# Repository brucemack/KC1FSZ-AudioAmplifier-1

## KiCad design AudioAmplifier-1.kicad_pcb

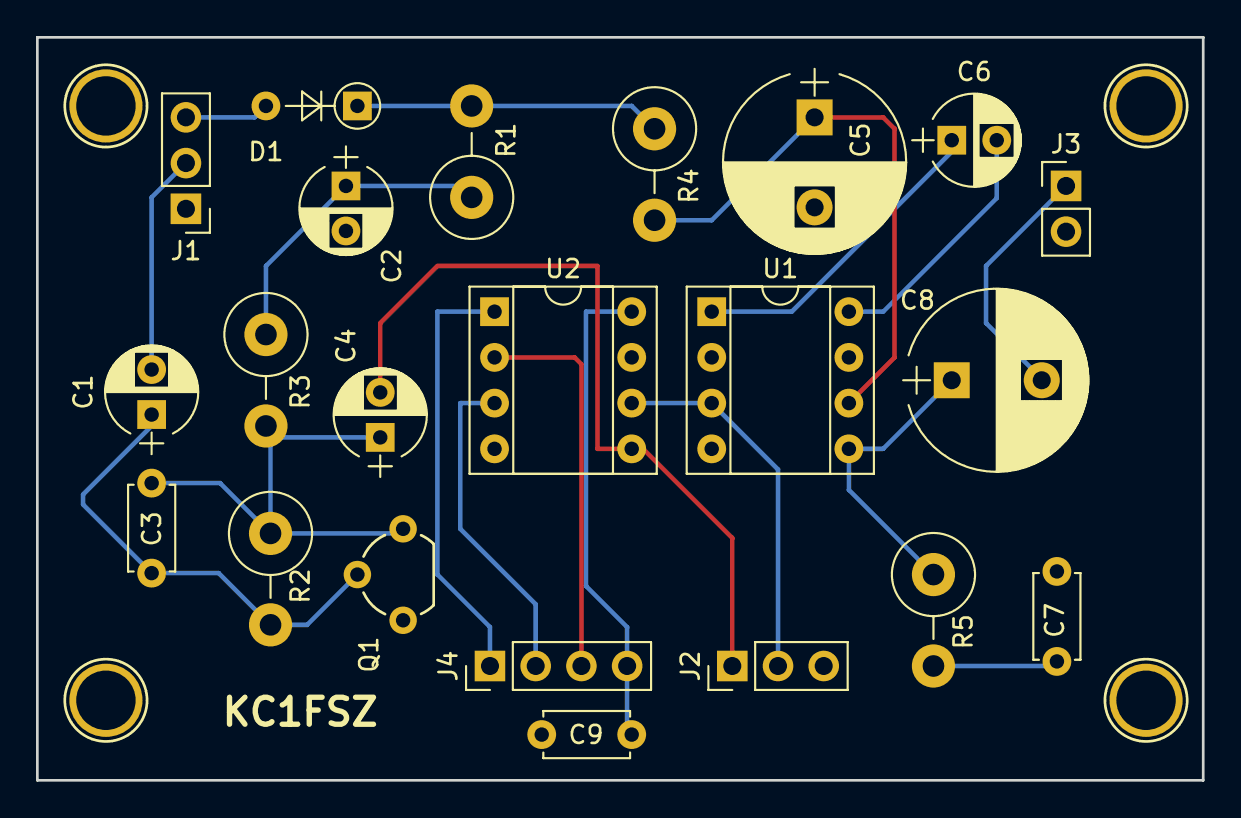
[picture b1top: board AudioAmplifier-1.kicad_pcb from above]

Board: 2 copper layers, 64.8 x 41.3 mm, 23 parts (0 on the bottom side), 19 nets.

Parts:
C1, C4: 1u; CP_Radial_D5.0mm_P2.50mm
C2, C6: CP; CP_Radial_D5.0mm_P2.50mm
C3: C; C_Disc_D4.7mm_W2.5mm_P5.00mm
C5: CP; CP_Radial_D10.0mm_P5.00mm
C7, C9: 0.1u; C_Disc_D4.7mm_W2.5mm_P5.00mm
C8: 470u; CP_Radial_D10.0mm_P5.00mm
D1: D; D_DO-35_SOD27_P5.08mm_Vertical_AnodeUp
J1, J2: Conn_01x03; Pin_Header_Straight_1x03_Pitch2.54mm
J3: Conn_01x02; Pin_Header_Straight_1x02_Pitch2.54mm
J4: Conn_01x04; Pin_Header_Straight_1x04_Pitch2.54mm
J5: Conn_01x01; 1pin
Q1: Q_NPN_EBC; TO-92_Molded_Wide
R1, R2, R3, R4: R; R_Axial_DIN0414_L11.9mm_D4.5mm_P5.08mm_Vertical
R5: 10; R_Axial_DIN0414_L11.9mm_D4.5mm_P5.08mm_Vertical
U1: LM386; DIP-8_W7.62mm_Socket
U2: MCP4131-103; DIP-8_W7.62mm_Socket

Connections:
GND: C2.2, C5.2, C7.2, C9.2, J1.1, J2.3, J3.2, J5.1, Q1.1, U1.2, U1.4, U2.4, U2.7
unnamed: C1.1, C3.2, Q1.2, R2.2
unnamed: C1.2, J1.2
unnamed: C2.1, R1.1, R3.1
unnamed: C3.1, C4.1, Q1.3, R2.1, R3.2
unnamed: C4.2, J2.1, U2.5
unnamed: C5.1, R4.2, U1.6
unnamed: C6.1, U1.1
unnamed: C6.2, U1.8
unnamed: C7.1, R5.2
unnamed: C8.1, R5.1, U1.5
unnamed: C8.2, J3.1
unnamed: C9.1, J4.4, U2.8
unnamed: D1.1, R1.2, R4.1
unnamed: D1.2, J1.3
unnamed: J2.2, U1.3, U2.6
unnamed: J4.1, U2.1
unnamed: J4.2, U2.3
unnamed: J4.3, U2.2

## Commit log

2018-06-19 Improved layout
